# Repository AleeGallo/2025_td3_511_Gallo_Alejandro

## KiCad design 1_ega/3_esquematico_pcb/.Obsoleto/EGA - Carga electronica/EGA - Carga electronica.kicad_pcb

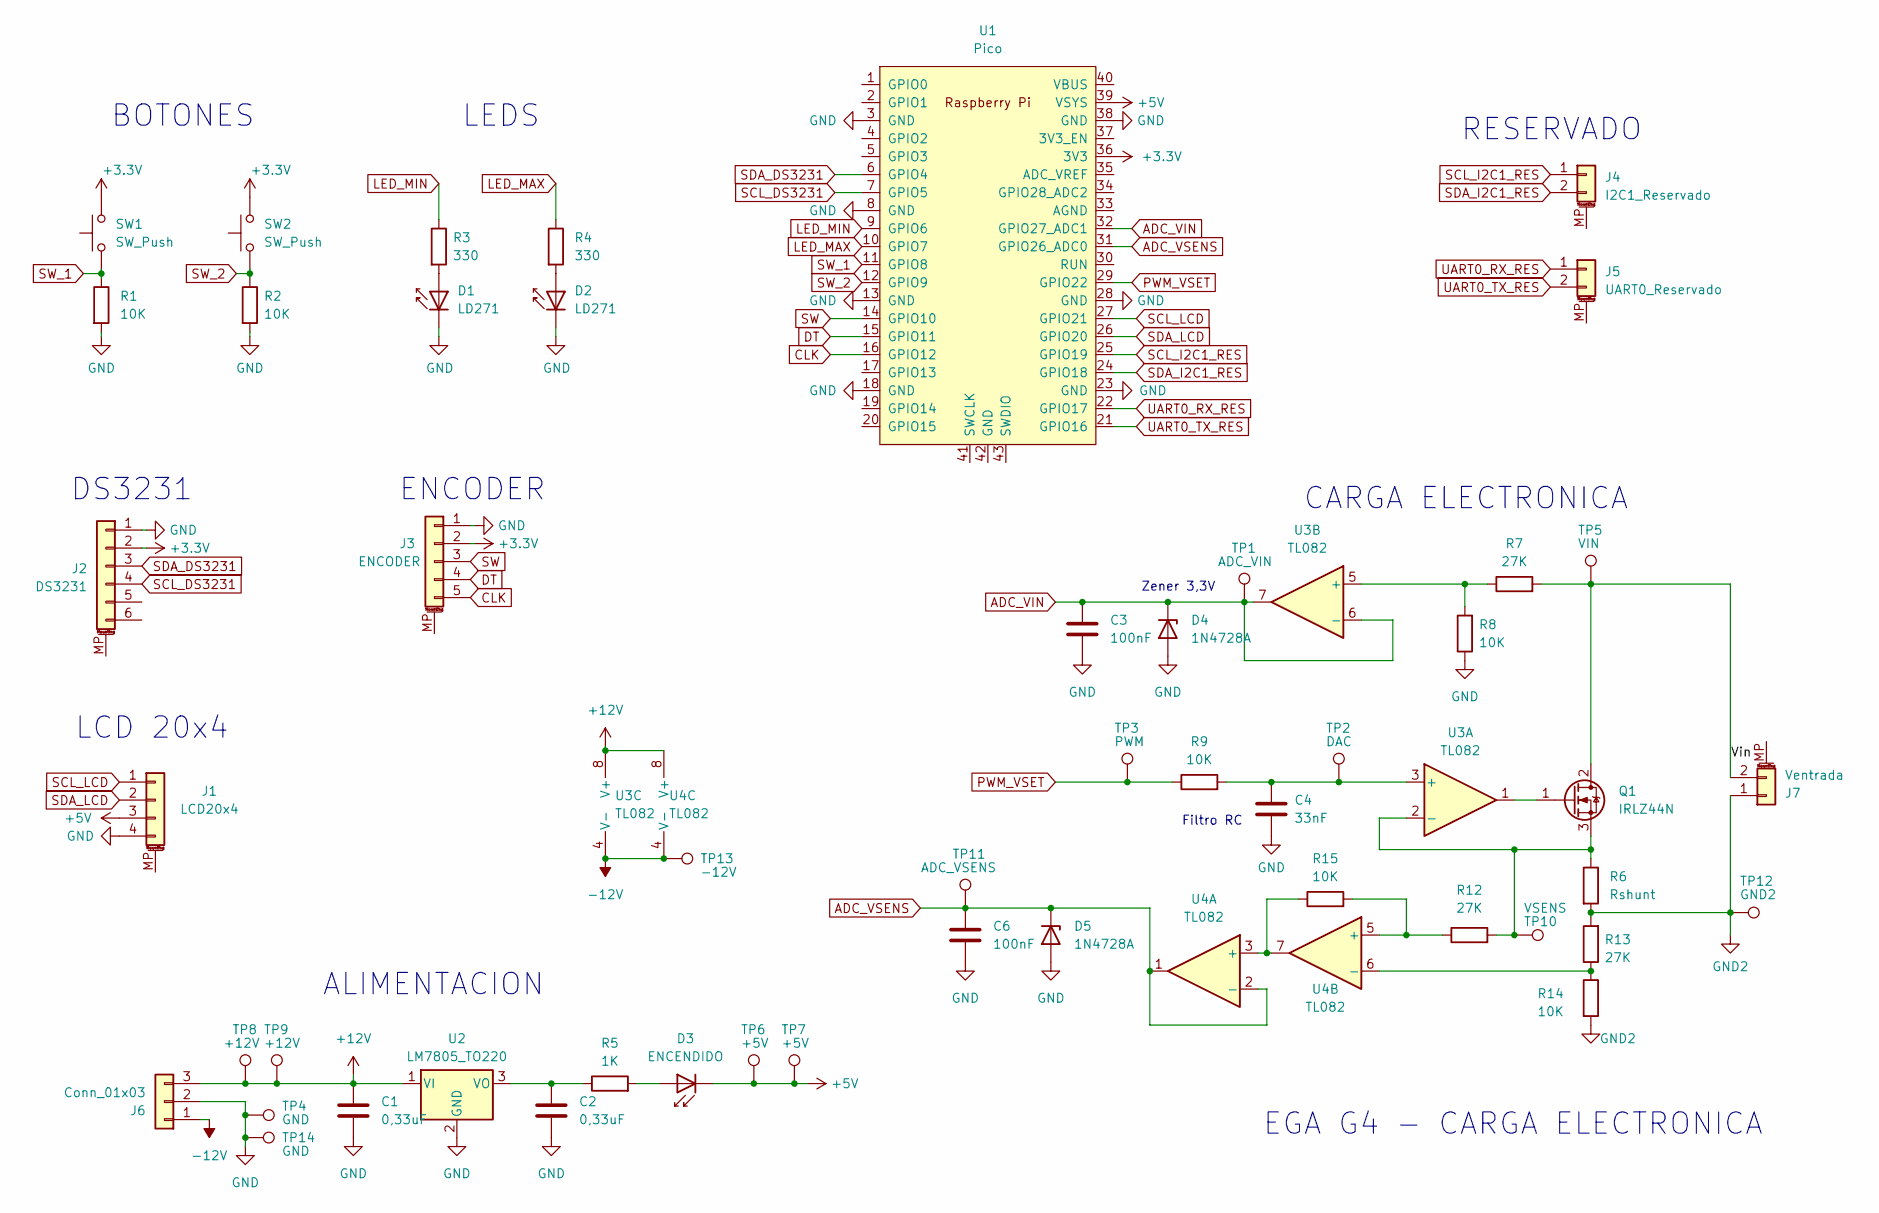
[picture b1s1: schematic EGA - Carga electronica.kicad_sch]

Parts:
C1, C2: 0,33uF; C_Disc_D7.0mm_W2.5mm_P5.00mm
C3, C6: 100nF; C_Disc_D7.0mm_W2.5mm_P5.00mm
C4: 33nF; C_Disc_D7.0mm_W2.5mm_P5.00mm
D1, D2: LD271; LED_D5.0mm_IRGrey
D3: ENCENDIDO; LED_D5.0mm_FlatTop
D4, D5: 1N4728A; D_DO-41_SOD81_P10.16mm_Horizontal
J1: LCD20x4; PinHeader_1x04_P2.54mm_Vertical
J2: DS3231; PinHeader_1x06_P2.54mm_Vertical
J3: ENCODER; PinHeader_1x05_P2.54mm_Vertical
J4: I2C1_Reservado; PinHeader_1x02_P2.54mm_Vertical
J5: UART0_Reservado; PinHeader_1x02_P2.54mm_Vertical
J6: Conn_01x03; TerminalBlock_Phoenix_MKDS-1,5-3-5.08_1x03_P5.08mm_Horizont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
J7: Ventrada; TerminalBlock_Phoenix_MKDS-1,5-2-5.08_1x02_P5.08mm_Horizont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
Q1: IRLZ44N; TO-220-3_Vertical
R1, R2, R8, R9, R14, R15: 10K; R_Axial_DIN0207_L6.3mm_D2.5mm_P7.62mm_Horizontal
R3, R4: 330; R_Axial_DIN0207_L6.3mm_D2.5mm_P7.62mm_Horizontal
R5: 1K; R_Axial_DIN0207_L6.3mm_D2.5mm_P7.62mm_Horizontal
R6: Rshunt; R_Axial_DIN0414_L11.9mm_D4.5mm_P15.24mm_Horizontal
R7, R12, R13: 27K; R_Axial_DIN0207_L6.3mm_D2.5mm_P7.62mm_Horizontal
SW1, SW2: SW_Push; SW_PUSH_6mm_H5mm
TP1: ADC_VIN; PinHeader_1x01_P2.54mm_Vertical
TP2: DAC; PinHeader_1x01_P2.54mm_Vertical
TP3: PWM; PinHeader_1x01_P2.54mm_Vertical
TP4, TP14: GND; PinHeader_1x01_P2.54mm_Vertical
TP5: VIN; PinHeader_1x01_P2.54mm_Vertical
TP6, TP7: +5V; PinHeader_1x01_P2.54mm_Vertical
TP8, TP9: +12V; PinHeader_1x01_P2.54mm_Vertical
TP10: VSENS; PinHeader_1x01_P2.54mm_Vertical
TP11: ADC_VSENS; PinHeader_1x01_P2.54mm_Vertical
TP12: GND2; PinHeader_1x01_P2.54mm_Vertical
TP13: -12V; PinHeader_1x01_P2.54mm_Vertical
U1: Pico; RPi_Pico_SMD_TH
U2: LM7805_TO220; TO-220-3_Vertical
U3, U4: TL082; DIP-8_W7.62mm_Socket_LongPads

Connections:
+3.3V: J2.2, J3.2, SW1.2, SW2.2, U1.36 (3V3)
+5V: D3.1 (K), J1.3, TP6.1, TP7.1, U1.39 (VSYS)
+12V: C1.1, J6.3, TP8.1, TP9.1, U2.1 (VI), U3.8 (V+), U4.8 (V+)
-12V: J6.1, TP13.1, U3.4 (V-), U4.4 (V-)
/Vin: J7.2, Q1.2 (D), R7.2, TP5.1
ADC_VIN: C3.1, D4.1 (K), TP1.1, U1.32 (GPIO27_ADC1), U3.6 (-), U3.7
ADC_VSENS: C6.1, D5.1 (K), TP11.1, U1.31 (GPIO26_ADC0), U4.1, U4.2 (-)
CLK: J3.5, U1.16 (GPIO12)
DT: J3.4, U1.15 (GPIO11)
GND: C1.2, C2.2, C3.2, C4.2, C6.2, D1.1 (K), D2.1 (K), D4.2 (A), D5.2 (A), J1.4, J2.1, J3.1, J6.2, R1.2, R2.2, R8.1, TP4.1, TP14.1, U1.3 (GND), U1.8 (GND), U1.13 (GND), U1.18 (GND), U1.23 (GND), U1.28 (GND), U1.38 (GND), U2.2 (GND)
GND2: J7.1, R6.2, R13.2, R14.2, TP12.1
LED_MAX: R4.1, U1.10 (GPIO7)
LED_MIN: R3.1, U1.9 (GPIO6)
unnamed: D1.2 (A), R3.2
unnamed: D2.2 (A), R4.2
unnamed: D3.2 (A), R5.2
unnamed: Q1.1 (G), U3.1
unnamed: Q1.3 (S), R6.1, R12.2, TP10.1, U3.2 (-)
unnamed: C2.1, R5.1, U2.3 (VO)
unnamed: C4.1, R9.2, TP2.1, U3.3 (+)
unnamed: R7.1, R8.2, U3.5 (+)
unnamed: R15.1, U4.3 (+), U4.7
unnamed: R12.1, R15.2, U4.5 (+)
unnamed: R13.1, R14.1, U4.6 (-)
PWM_VSET: R9.1, TP3.1, U1.29 (GPIO22)
SCL_DS3231: J2.4, U1.7 (GPIO5)
SCL_I2C1_RES: J4.1, U1.25 (GPIO19)
SCL_LCD: J1.1, U1.27 (GPIO21)
SDA_DS3231: J2.3, U1.6 (GPIO4)
SDA_I2C1_RES: J4.2, U1.24 (GPIO18)
SDA_LCD: J1.2, U1.26 (GPIO20)
SW: J3.3, U1.14 (GPIO10)
SW_1: R1.1, SW1.1, U1.11 (GPIO8)
SW_2: R2.1, SW2.1, U1.12 (GPIO9)
UART0_RX_RES: J5.1, U1.22 (GPIO17)
UART0_TX_RES: J5.2, U1.21 (GPIO16)

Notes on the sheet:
LCD 20x4
EGA G4 - CARGA ELECTRONICA
Zener 3,3V
Filtro RC
ALIMENTACION
BOTONES
CARGA ELECTRONICA
RESERVADO
ENCODER
DS3231
LEDS

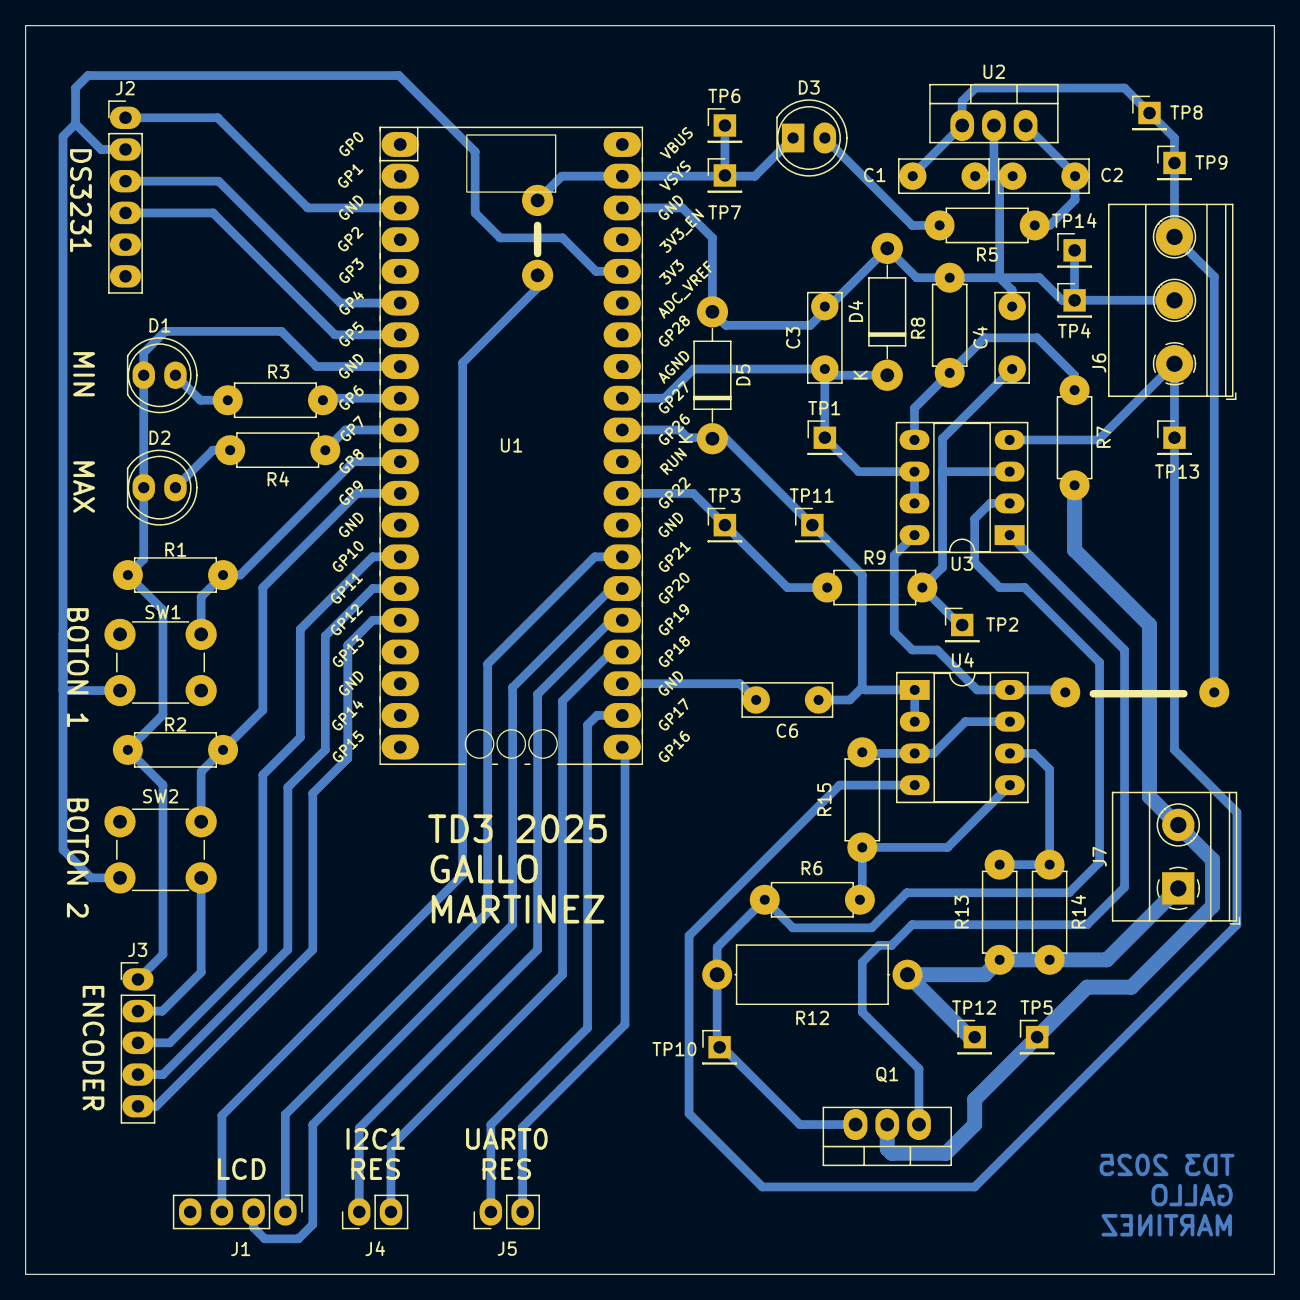
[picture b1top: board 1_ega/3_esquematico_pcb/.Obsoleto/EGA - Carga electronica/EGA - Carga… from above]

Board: 2 copper layers, 100.0 x 100.0 mm, 51 parts (0 on the bottom side), 36 nets.

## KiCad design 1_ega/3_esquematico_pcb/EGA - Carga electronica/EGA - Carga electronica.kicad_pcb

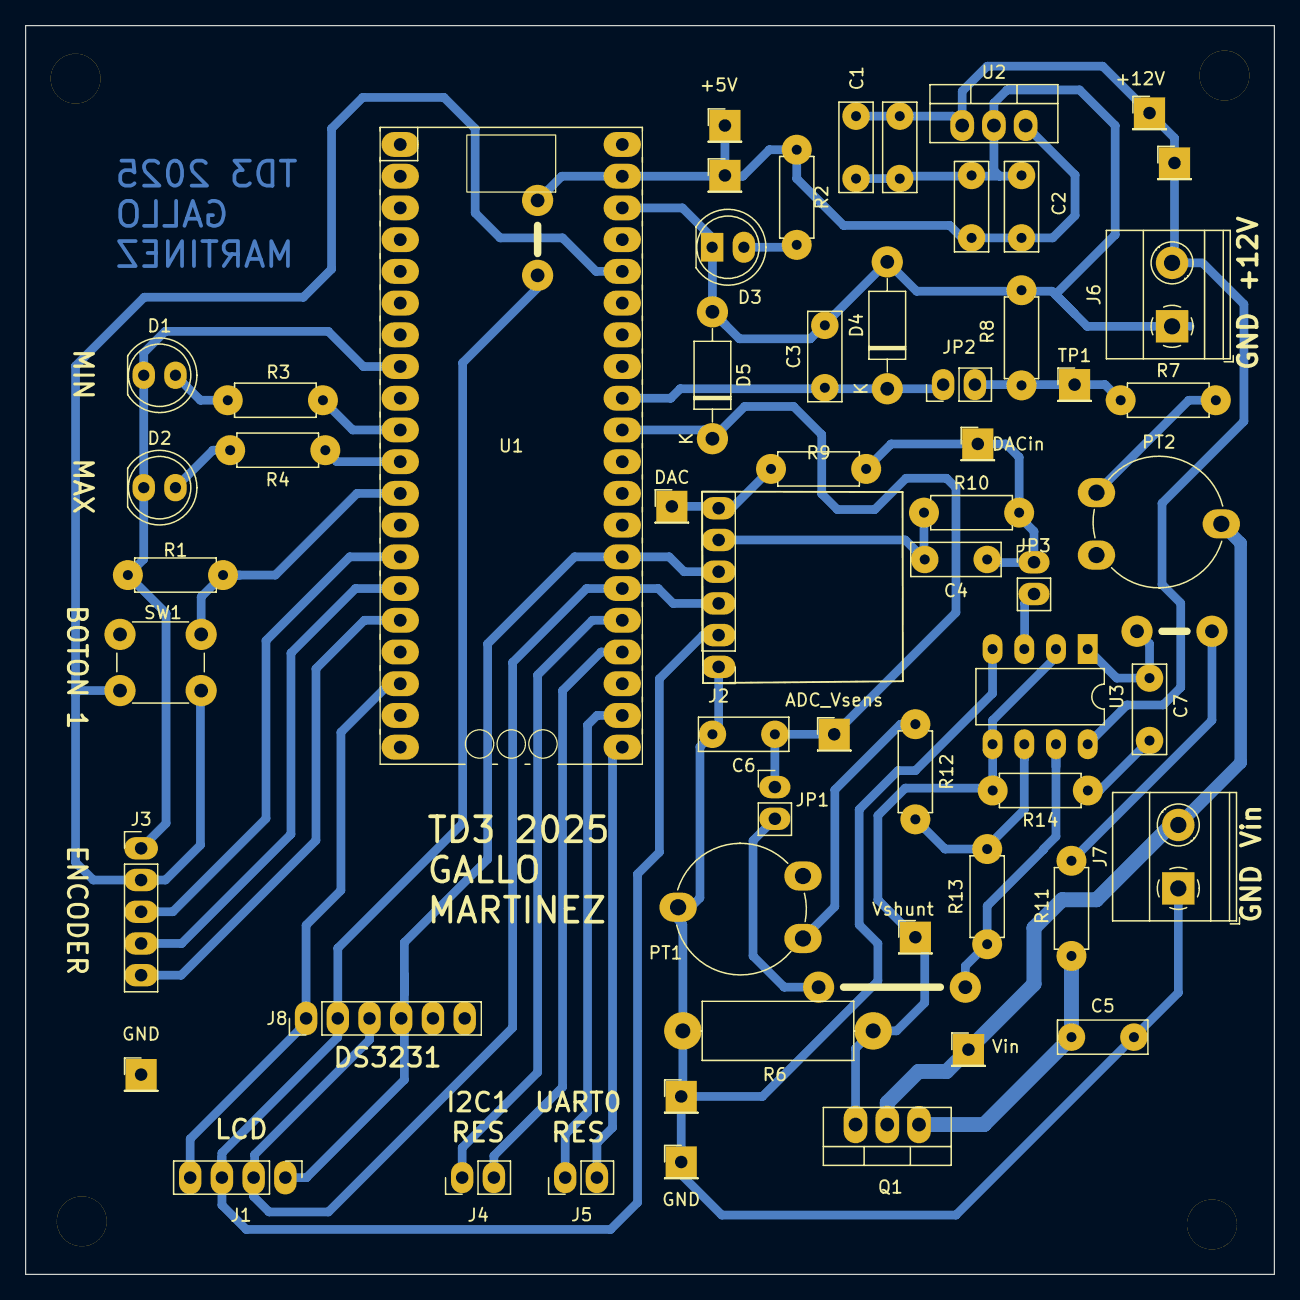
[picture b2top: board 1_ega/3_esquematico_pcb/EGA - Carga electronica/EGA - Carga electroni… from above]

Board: 2 copper layers, 100.0 x 100.0 mm, 58 parts (0 on the bottom side), 35 nets.

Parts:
+5V: +5V; PinHeader_1x01_P2.54mm_Vertical
+12V: +12V; PinHeader_1x01_P2.54mm_Vertical
ADC_Vsens: ADC_VSENS; PinHeader_1x01_P2.54mm_Vertical
C1, C1#2, C2, C2#2: 0,33uF; C_Disc_D7.0mm_W2.5mm_P5.00mm
C3, C4, C6: 100nF; C_Disc_D7.0mm_W2.5mm_P5.00mm
C5: 10nF; C_Disc_D7.0mm_W2.5mm_P5.00mm
C7: 1nF; C_Disc_D7.0mm_W2.5mm_P5.00mm
D1, D2: LD271; LED_D5.0mm_IRGrey
D3: ENCENDIDO; LED_D5.0mm_FlatTop
D4, D5: 1N4728A; D_DO-41_SOD81_P10.16mm_Horizontal
DAC: VDAC; PinHeader_1x01_P2.54mm_Vertical
DACin: DAC; PinHeader_1x01_P2.54mm_Vertical
GND: GND; PinHeader_1x01_P2.54mm_Vertical
GND#2: GND2; PinHeader_1x01_P2.54mm_Vertical
J1: LCD20x4; PinHeader_1x04_P2.54mm_Vertical
J2: MCP4725; PinHeader_1x06_P2.54mm_Vertical
J3: ENCODER; PinHeader_1x05_P2.54mm_Vertical
J4: I2C1_Reservado; PinHeader_1x02_P2.54mm_Vertical
J5: UART0_Reservado; PinHeader_1x02_P2.54mm_Vertical
J6: V+; TerminalBlock_Phoenix_MKDS-1,5-2-5.08_1x02_P5.08mm_Horizont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
J7: Ventrada; TerminalBlock_Phoenix_MKDS-1,5-2-5.08_1x02_P5.08mm_Horizont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
J8: DS3231; PinHeader_1x06_P2.54mm_Vertical
JP1, JP2, JP3: Jumper; PinHeader_1x02_P2.54mm_Vertical
PT1, PT2: PRESET 1K; Potentiometer_Piher_PT-10-V10_Vertical
Q1: IRFZ44; TO-220-3_Vertical
R1, R9, R10, R12, R14: 10K; R_Axial_DIN0207_L6.3mm_D2.5mm_P7.62mm_Horizontal
R2: 1K; R_Axial_DIN0207_L6.3mm_D2.5mm_P7.62mm_Horizontal
R3, R4: 330; R_Axial_DIN0207_L6.3mm_D2.5mm_P7.62mm_Horizontal
R6: Rshunt; R_Axial_DIN0414_L11.9mm_D4.5mm_P15.24mm_Horizontal
R7: 12K; R_Axial_DIN0207_L6.3mm_D2.5mm_P7.62mm_Horizontal
R8: 4,7K; R_Axial_DIN0207_L6.3mm_D2.5mm_P7.62mm_Horizontal
R11: 100; R_Axial_DIN0207_L6.3mm_D2.5mm_P7.62mm_Horizontal
R13: 3,3K; R_Axial_DIN0207_L6.3mm_D2.5mm_P7.62mm_Horizontal
SW1: SW_Push; SW_PUSH_6mm_H5mm
TP1: ADC_VIN; PinHeader_1x01_P2.54mm_Vertical
TP7: +5V; PinHeader_1x01_P2.54mm_Vertical
TP9: +12V; PinHeader_1x01_P2.54mm_Vertical
TP14: GND; PinHeader_1x01_P2.54mm_Vertical
U1: Pico; RPi_Pico_SMD_TH
U2: LM7805_TO220; TO-220-3_Vertical
U3: LM358; DIP-8_W7.62mm_LongPads
Vin: VIN; PinHeader_1x01_P2.54mm_Vertical
Vshunt: VSENS; PinHeader_1x01_P2.54mm_Vertical

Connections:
+3.3V: J3.2, SW1.2, U1.36 (3V3)
+5V: +5V.1, C2.1, C2#2.1, J1.3, J2.2, J8.2, R2.2, TP7.1, U1.39 (VSYS), U2.3 (VO)
+12V: +12V.1, C1.1, C1#2.1, J6.2, TP9.1, U2.1 (VI), U3.8 (V+)
/Vin: J7.2, PT2.2, Q1.2 (D), Vin.1
ADC_VIN: C3.1, D4.1 (K), JP2.1 (A), U1.32 (GPIO27_ADC1)
ADC_VSENS: ADC_Vsens.1, C6.1, D5.1 (K), JP1.1 (A), U1.31 (GPIO26_ADC0)
CLK: J3.5, U1.16 (GPIO12)
DAC: DAC.1, J2.6, R9.1
DT: J3.4, U1.15 (GPIO11)
GND: C1.2, C1#2.2, C2.2, C2#2.2, C3.2, C5.2, C6.2, D1.1 (K), D2.1 (K), D3.1 (K), D4.2 (A), D5.2 (A), GND.1, GND#2.1, J1.4, J2.1, J3.1, J6.1, J7.1, J8.1, PT1.2, R1.2, R6.2, R8.1, TP14.1, U1.3 (GND), U1.8 (GND), U1.13 (GND), U1.18 (GND), U1.23 (GND), U1.28 (GND), U1.38 (GND), U2.2 (GND), U3.4 (V-)
GND2: C4.2, J2.5, R10.1
LED_MAX: R4.1, U1.11 (GPIO8)
LED_MIN: R3.1, U1.10 (GPIO7)
unnamed: C7.1, R14.1
unnamed: C7.2, R11.2, U3.1
unnamed: D1.2 (A), R3.2
unnamed: D2.2 (A), R4.2
unnamed: D3.2 (A), R2.1
unnamed: JP1.2 (B), R13.2, U3.7
unnamed: JP2.2 (B), R7.1, R8.2, TP1.1
unnamed: C4.1, DACin.1, JP3.1 (A), R9.2, R10.2
unnamed: JP3.2 (B), U3.3 (+)
unnamed: PT1.3, R12.1
unnamed: PT2.3, R7.2
unnamed: C5.1, Q1.1 (G), R11.1
unnamed: Q1.3 (S), R6.1, R14.2, U3.2 (-), U3.5 (+), Vshunt.1
unnamed: R12.2, R13.1, U3.6 (-)
SCL_I2C0: J1.1, J2.4, J8.4, U1.27 (GPIO21)
SCL_I2C1_RES: J4.1, U1.25 (GPIO19)
SDA_I2C0: J1.2, J2.3, J8.3, U1.26 (GPIO20)
SDA_I2C1_RES: J4.2, U1.24 (GPIO18)
SW: J3.3, U1.14 (GPIO10)
SW_CONFIG: R1.1, SW1.1, U1.12 (GPIO9)
UART0_RX_RES: J5.1, U1.22 (GPIO17)
UART0_TX_RES: J5.2, U1.21 (GPIO16)

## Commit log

2025-05-29 Primer consigna de TP3
2025-06-02 Segunda consigna de TP3
2025-07-05 EGA V1
2025-07-19 ega/v2
2025-07-26 Avance 1
2025-07-28 Avance 2
2025-07-29 Tareas LCD y Config
2025-07-31 Anda configuracion Vmax, Imax y R
2025-07-31 Se agrega muestreo de configuracion cada 2 segundos, queda solucionar el segundo renglon cuando se muestra. Ver tarea EEPROM
2025-08-04 Se modifica Config para enviar por Queue_EEPROM de a 1 dato. Se avanzara con guardado en EEPROM y RTC
2025-08-05 Se agrega task_EEPROM, se suma SemMutex y ajustes en Config. Prox pasos probar que la escritura y la lectura funcione OK
2025-08-06 Agrego codigo en tarea EEPROM
2025-08-06 Se agregan Sem Mutex y Sem Config al codigo
2025-08-08 EEPROM y RTC funcionando. RTC no devuelve fecha y hora, hay que revisar. Se avanzara con flujo de tareas. Cambio diagrama de pines por I2C
2025-08-09 RTC y EEPROM funcionando. Cada vez que se setea el valor, se guarda y se muestra en pantalla junto a la hora. Tareas CONFIG, EEPROM y LCD funcionando
2025-08-09 Se agregan tareas y colas al codigo. Se avanzara con las tareas de funcionamiento continuo de la carga
2025-08-10 Se actualiza codigo con submodulos mcp4725 y ds3231
2025-08-10 Acomodo submodulos
2025-08-13 Se agregan en Config los valores minimos y tiempo entre repeticion
2025-08-13 Se agrega task_Sensado
2025-08-13 Se agregan tareas Resistencia y ADC, se avanza con PID. DAC y ADC fisicamente funcionando bien.
2025-08-13 Se agrega tarea PID
2025-08-19 Ultima actualizacion EGA primer fecha
2025-08-21 Adecuacion de tareas y funciones
2025-08-22 Funcionando task_Resistencia y medicion en modo activo. Se simulan valores
2025-08-24 Se actualiza alarmas
2025-08-25 Se agregan y casi terminan las alarmas
2025-08-26 Actualizaciones con alarmas
2025-08-26 Archivo de mediciones
2025-08-27 PID finalizado, se ultiman detalles. Falta revisar utilizacion completa con alarmas
2025-08-27 Finalización del código, agregado del cuestionario
2025-09-03 Informacion completa final. Entrega v3
2025-11-04 Actualiza codigo firmware
2025-11-04 Actualizaciones varias
2025-11-04 Sac debugprobe
2025-11-04 Se modifican Colas y comunicacion entre tareas
2025-11-05 Vuelvo a actualizar laboral
2025-11-05 Quito repos embebidos del index
2025-11-05 Quito repos del index
2025-11-05 Segunda consigna del TP4
2025-11-05 Primer consigna del TP5
2025-11-05 Segunda consigna del TP5
2025-11-06 Se modifican puntos de EGA
2025-11-08 Se corrige codigo entre tareas de EGA
2025-11-11 Funcionando estado config. Aun no se logra el funcionamiento completo
2025-11-13 EGA funcionando OK. Faltan ajustes finos porque se traba despues de un rato
2025-11-16 Fin EGA funcionando con arreglos. Comienzo EGB
2025-11-18 Se agregan funciones UART y se pasa a EGB
2025-11-24 Actualizaciones de EGB. Pruebas del driver
2025-11-24 Paso archivos
2025-11-24 Se cargan archivos
2025-11-24 Actualizo Linux
2025-11-27 Actualizaciones varias del driver
2025-11-30 DRIVER FUNCIONANDO. Kernel OK. RTOS se rompio, copia de seguridad para modificarlo
2025-12-03 Actualizaciones RTOS. GPOS funcionando OK. CLI y GUI funcionando OK. Se avanza con informe
2025-12-09 Se realiza informe EGB, actualiza informe EGA. Codigo funcionando, se mejora driver para evitar errores de GET/sET desfazado
2025-12-10 Carga de informe. Presentacion de EGB v1.
2025-12-10 EGB completo. Se agrega video del funcionamiento
